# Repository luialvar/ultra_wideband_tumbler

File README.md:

# Tumbler UWB Subsystem Workspace

This repository organizes the hardware, mechanical-design, power-analysis, embedded-driver, and firmware material for the Tumbler UWB node in the AMADEE-27 university robotics project. The software migration from the older SKITH/DWM1000 platform to a newer STM32L4/DWM3000 PCB is a central part of the work, but it is not the whole project: the repository also captures the PCB, mechanical-integration, power-budget, and bring-up context needed to make the Tumbler subsystem usable.

The project is intentionally split by layer. The legacy folders are kept as engineering references, while the new CubeMX firmware and the Tumbler PCB are the active migration target.

## Project Context: AMADEE-27

This work was developed in the context of a university robotics project preparing a contribution for AMADEE-27, an international Mars analog mission managed by the Austrian Space Forum (OeWF).

AMADEE-27 is designed to emulate selected aspects of a human-robotic Mars mission. The mission concept combines analog astronauts, robotic systems, field experiments, and a Mission Support Center in Austria to recreate operational constraints similar to planetary exploration. The official AMADEE-27 call focuses on areas such as engineering and robotics, planetary surface operations, geoscience, life sciences, and human factors.

Within that broader university project, my responsibility was the Tumbler UWB subsystem rather than only a code port. That included understanding the old UWB localization stack, contributing to mechanical design and integration ideas, helping around the new PCB by studying the schematic/layout and matching it to firmware pin names, learning the practical hardware constraints, documenting the PCB and power-budget context, and preparing the new STM32CubeMX/HAL firmware structure for the upgraded PCB.

External context:

- Austrian Space Forum AMADEE-27 overview: https://oewf.org/en/amadee-27/
- AMADEE-27 Announcement of Opportunity: https://oewf.org/en/2025/12/amadee-27-ao/

## Tumbler Subsystem Scope

The important object in this repository is the Tumbler UWB subsystem as an integrated robot component. In practice, that means the work spans several connected areas:

- mechanical design exploration for fitting the electronics into the Tumbler concept,
- support and learning around the new PCB design, including how schematic/layout choices become firmware pin definitions,
- power-budget tracking for tag and anchor operating assumptions,
- low-level STM32L4/DWM3000 bring-up,
- migration of the old UWB ranging ideas onto a new CubeMX/HAL and Qorvo DW3xxx base.

The firmware migration is therefore one part of a larger embedded-system integration effort.

## Migration Summary

| Layer | Legacy platform | New platform |
| --- | --- | --- |
| Hardware | DWM1000-based SKITH board | DWM3000-based Tumbler board |
| Microcontroller | STM32F407 | STM32L431 |
| Framework | RODOS and legacy board wrappers | STM32Cube HAL generated by CubeMX |
| UWB driver | Decawave DWM1000 API | Qorvo DW3xxx driver |
| Application | Legacy tag/anchor ranging code | New CubeMX firmware for the new PCB |

## Repository Map

| Folder | Purpose |
| --- | --- |
| `SKITH_old_PCB/` | Legacy PCB design for the old SKITH UWB node. It represents the old hardware side of the DWM1000/STM32F407 platform. |
| `Tumbler_new_PCB/` | New PCB design for the upgraded UWB node. It contains the KiCad project, schematic sheets, layout, 3D exports, and production outputs for the DWM3000/STM32L431 board. |
| `power_calculations/` | Spreadsheet-based power budgets. The files are grouped around the old and new PCB assumptions, including anchor/tag operating modes. |
| `old_uwb_reference_repo/` | Legacy university toolkit component used as a software reference. It contains the old embedded DWM1000 firmware plus robot-side ROS localization code. |
| `software_new_pcb/` | New STM32CubeMX/HAL firmware for the new PCB. This is the active new-board software area. |
| `tumbler_images/` | Mechanical concept images and visual material for the Tumbler integration work. |
| `useful_links.txt` | Extra project links and references collected during development. |

## What Is Reused

The useful software inheritance is at the protocol level, not at the low-level driver level. The legacy code is valuable because it already contains the tag/anchor ranging flow, message types, timestamp packing, and two-way-ranging state machine. Those concepts can be ported to the new firmware.

The old Decawave DWM1000 driver, the RODOS scheduling code, the old SPI/GPIO wrappers, and the old board calibration constants should not be copied directly into the new STM32L431/DWM3000 firmware.

## Current Engineering Focus

The new firmware is built around STM32Cube HAL and the Qorvo DW3xxx driver. CubeMX describes the real wiring from the new PCB, including SPI, IRQ, reset, wakeup, power-control, and BMS-related pins. The firmware then uses those generated names in the board-port layer so that the UWB driver can talk to the DWM3000 through the actual hardware connections.

The practical bring-up path is:

1. Validate the CubeMX pin map against the Tumbler PCB schematic.
2. Bring up SPI, reset, wakeup, chip-select, and IRQ in the STM32 port layer.
3. Read the DW3xxx device ID through the Qorvo driver.
4. Test raw TX/RX frames.
5. Port the old tag/anchor ranging logic onto the new driver and HAL base.
6. Recalibrate antenna delays and timing for the new board.

## Engineering Highlights

This repository demonstrates a full embedded migration across hardware, firmware, and tooling boundaries:

- connecting mechanical integration constraints with the electronics layout,
- helping translate the new PCB design into a firmware-facing pin map,
- translating real PCB wiring into CubeMX/HAL pin definitions,
- replacing a legacy DWM1000 driver stack with the Qorvo DW3xxx driver,
- separating reusable ranging logic from non-reusable board/framework code,
- keeping only the required DW3xxx driver sources inside the firmware tree instead of storing the full vendor SDK,
- connecting firmware operating modes to spreadsheet-based power estimates.

## Notes for Reviewers

This repository is a migration and integration workspace, so it intentionally contains both original references and new implementation work. The separation is important: hardware design files document the boards, the power spreadsheets document expected operating modes, and the CubeMX firmware is where the new embedded software and DW3xxx driver integration are implemented.

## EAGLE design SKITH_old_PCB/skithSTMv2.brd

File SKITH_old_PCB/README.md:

# SKITH Old PCB

This folder contains the legacy PCB design for the older SKITH UWB node used as the starting point of the migration.

In the overall project, this is the old hardware reference:

| Layer | Value |
| --- | --- |
| UWB module | DWM1000 |
| Microcontroller family | STM32F407 |
| Firmware stack used with this board | RODOS, legacy wrappers, Decawave DWM1000 API |
| Role in this repository | Hardware reference for the legacy platform |

## Contents

| File or folder | Purpose |
| --- | --- |
| `skithSTMv2.kicad_pro` | KiCad project entry point. Open this file in KiCad to inspect the board. |
| `skithSTMv2.kicad_pcb` | PCB layout. |
| `skithSTMv2.sch` | Legacy schematic file. |
| `Schaltplan_Skith_STM_2.pdf` | PDF schematic export for quick review. |
| `skithSTMv2.brd` | Board file from the older design flow. |
| `sym-lib-table` | KiCad symbol-library configuration. |
| `skithSTMv2.kicad_dru` | KiCad design-rule settings. |
| `skithSTMv2.kicad_prl` | KiCad local/session state; useful for KiCad, but not part of the engineering design itself. |

## How This Fits the Migration

This board is not the firmware target for the new implementation. It is included so the old DWM1000/STM32F407 hardware can be compared against the new DWM3000/STM32L431 design.

The old firmware associated with this hardware is kept separately in `../old_uwb_reference_repo/embedded_uwb/`. The PCB files here describe the electrical design: connectors, MCU pins, UWB module wiring, power rails, and board layout.

For the new board, see `../Tumbler_new_PCB/`.

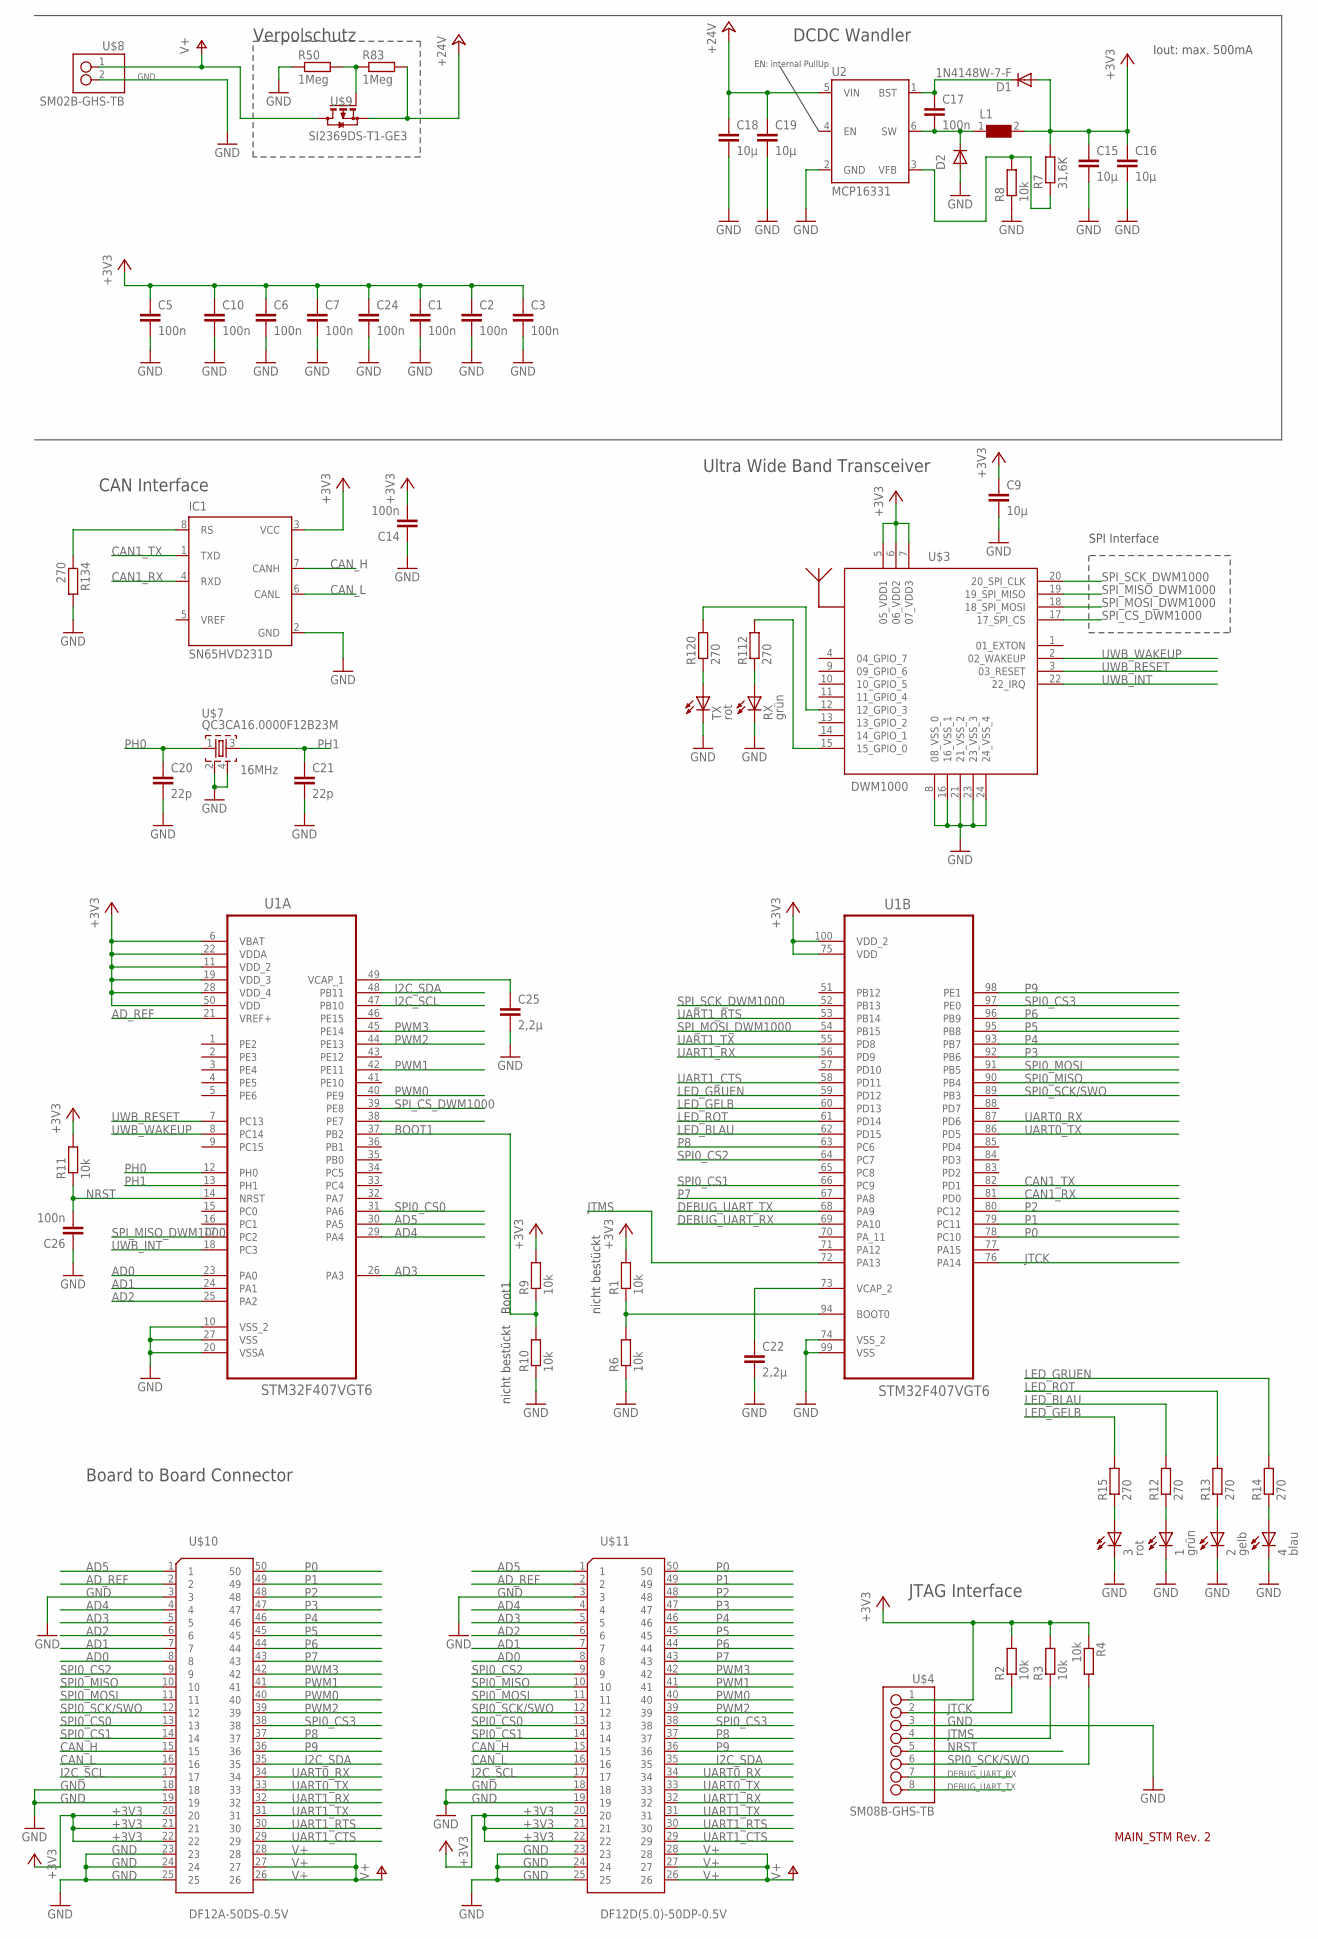
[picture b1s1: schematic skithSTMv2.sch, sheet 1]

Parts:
1: grün; SML0603
2: gelb; SML0603
3: rot; SML0603
4: blau; SML0603
C1, C2, C3, C5, C6, C7, C10, C14, C17, C24, C26: 100n; C0402
C9, C15, C16, C18, C19: 10µ; C0805
C20, C21: 22p; C0402
C22, C25: 2,2µ; C0402
D1: 1N4148W-7-F; SOD123
D2: DIODE-DO214AC; DO214AC
IC1: SN65HVD231D; SO8
L1: WE-TPC-744025150_2828; WE-TPC_2828
R1, R2, R3, R4, R6, R8, R9, R10, R11: 10k; R0402
R7: 31,6K; R0402
R12, R13, R14, R15, R112, R120, R134: 270; R0402
R50, R83: 1Meg; R0402
RX: grün; SML0603
TX: rot; SML0603
U1: STM32F407VGT6; QFP50P1600X1600X160-100N
U2: MCP16331; SOT23-6
U$3: DWM1000
U$4: SM08B-GHS-TB
U$7: QC3CA16.0000F12B23M; LFXTAL055998
U$8: SM02B-GHS-TB
U$9: SI2369DS-T1-GE3; SOT23
U$10: DF12A-50DS-0.5V
U$11: DF12D(5.0)-50DP-0.5V

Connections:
+3V3: C1.1, C2.1, C3.1, C5.1, C6.1, C7.1, C9.1, C10.1, C14.2, C15.1, C16.1, C24.1, D1.A, IC1.3 (VCC), L1.2, R1.2, R2.2, R3.2, R4.1, R7.2, R9.2, R11.2, U1.6 (VBAT), U1.11 (VDD_2), U1.19 (VDD_3), U1.22 (VDDA), U1.28 (VDD_4), U1.50 (VDD), U1.75 (VDD), U1.100 (VDD_2), U$3.5 (05_VDD1), U$3.6 (06_VDD2), U$3.7 (07_VDD3), U$4.1, U$10.20, U$10.21, U$10.22, U$11.20, U$11.21, U$11.22
+24V: C18.1, C19.1, R83.2, U2.5 (VIN), U$9.2 (S)
AD0: U1.23 (PA0), U$10.8, U$11.8
AD1: U1.24 (PA1), U$10.7, U$11.7
AD2: U1.25 (PA2), U$10.6, U$11.6
AD3: U1.26 (PA3), U$10.5, U$11.5
AD4: U1.29 (PA4), U$10.4, U$11.4
AD5: U1.30 (PA5), U$10.1, U$11.1
AD_REF: U1.21 (VREF+), U$10.2, U$11.2
BOOT1: R9.1, R10.2, U1.37 (PB2)
CAN1_RX: IC1.4 (RXD), U1.81 (PD0)
CAN1_TX: IC1.1 (TXD), U1.82 (PD1)
CAN_H: IC1.7 (CANH), U$10.15, U$11.15
CAN_L: IC1.6 (CANL), U$10.16, U$11.16
DEBUG_UART_RX: U1.69 (PA10), U$4.7
DEBUG_UART_TX: U1.68 (PA9), U$4.8
GND: 1.C, 2.C, 3.C, 4.C, C1.2, C2.2, C3.2, C5.2, C6.2, C7.2, C9.2, C10.2, C14.1, C15.2, C16.2, C18.2, C19.2, C20.2, C21.2, C22.2, C24.2, C25.2, C26.1, D2.A, IC1.2 (GND), R6.1, R8.1, R10.1, R50.1, R134.2, RX.C, TX.C, U1.10 (VSS_2), U1.20 (VSSA), U1.27 (VSS), U1.74 (VSS_2), U1.99 (VSS), U2.2 (GND), U$3.8 (08_VSS_0), U$3.16 (16_VSS_1), U$3.21 (21_VSS_2), U$3.23 (23_VSS_3), U$3.24 (24_VSS_4), U$4.3, U$7.2, U$7.4, U$8.2, U$10.3, U$10.18, U$10.19, U$10.23, U$10.24, U$10.25, U$11.3, U$11.18, U$11.19, U$11.23, U$11.24, U$11.25
I2C_SCL: U1.47 (PB10), U$10.17, U$11.17
I2C_SDA: U1.48 (PB11), U$10.35, U$11.35
JTCK: R2.1, U1.76 (PA14), U$4.2
JTMS: R3.1, U1.72 (PA13), U$4.4
LED_BLAU: R12.2, U1.62 (PD15)
LED_GELB: R15.2, U1.60 (PD13)
LED_GRUEN: R14.2, U1.59 (PD12)
LED_ROT: R13.2, U1.61 (PD14)
unnamed: C22.1, U1.73 (VCAP_2)
unnamed: R112.2, U$3.15 (15_GPIO_0)
unnamed: R7.1, R8.2, U2.3 (VFB)
unnamed: C17.1, D1.C, U2.1 (BST)
unnamed: C17.2, D2.C, L1.1, U2.6 (SW)
unnamed: 1.A, R12.1
unnamed: 2.A, R13.1
unnamed: 4.A, R14.1
unnamed: R1.1, R6.2, U1.94 (BOOT0)
unnamed: 3.A, R15.1
unnamed: C25.1, U1.49 (VCAP_1)
unnamed: IC1.8 (RS), R134.1
unnamed: R112.1, RX.A
unnamed: R120.1, TX.A
unnamed: R120.2, U$3.12 (12_GPIO_3)
unnamed: R50.2, R83.1, U$9.1 (G)
NRST: C26.2, R11.1, U1.14 (NRST), U$4.5
P0: U1.78 (PC10), U$10.50, U$11.50
P1: U1.79 (PC11), U$10.49, U$11.49
P2: U1.80 (PC12), U$10.48, U$11.48
P3: U1.92 (PB6), U$10.47, U$11.47
P4: U1.93 (PB7), U$10.46, U$11.46
P5: U1.95 (PB8), U$10.45, U$11.45
P6: U1.96 (PB9), U$10.44, U$11.44
P7: U1.67 (PA8), U$10.43, U$11.43
P8: U1.63 (PC6), U$10.37, U$11.37
P9: U1.98 (PE1), U$10.36, U$11.36
PH0: C20.1, U1.12 (PH0), U$7.1
PH1: C21.1, U1.13 (PH1), U$7.3
PWM0: U1.40 (PE9), U$10.40, U$11.40
PWM1: U1.42 (PE11), U$10.41, U$11.41
PWM2: U1.44 (PE13), U$10.39, U$11.39
PWM3: U1.45 (PE14), U$10.42, U$11.42
SPI0_CS0: U1.31 (PA6), U$10.13, U$11.13
SPI0_CS1: U1.66 (PC9), U$10.14, U$11.14
SPI0_CS2: U1.64 (PC7), U$10.9, U$11.9
SPI0_CS3: U1.97 (PE0), U$10.38, U$11.38
SPI0_MISO: U1.90 (PB4), U$10.10, U$11.10
SPI0_MOSI: U1.91 (PB5), U$10.11, U$11.11
SPI0_SCK/SWO: R4.2, U1.89 (PB3), U$4.6, U$10.12, U$11.12
SPI_CS_DWM1000: U1.39 (PE8), U$3.17 (17_SPI_CS)
SPI_MISO_DWM1000: U1.17 (PC2), U$3.19 (19_SPI_MISO)
SPI_MOSI_DWM1000: U1.54 (PB15), U$3.18 (18_SPI_MOSI)
SPI_SCK_DWM1000: U1.52 (PB13), U$3.20 (20_SPI_CLK)
UART0_RX: U1.87 (PD6), U$10.34, U$11.34
UART0_TX: U1.86 (PD5), U$10.33, U$11.33
UART1_CTS: U1.58 (PD11), U$10.29, U$11.29
UART1_RTS: U1.53 (PB14), U$10.30, U$11.30
UART1_RX: U1.56 (PD9), U$10.32, U$11.32
UART1_TX: U1.55 (PD8), U$10.31, U$11.31
UWB_INT: U1.18 (PC3), U$3.22 (22_IRQ)
UWB_RESET: U1.7 (PC13), U$3.3 (03_RESET)
UWB_WAKEUP: U1.8 (PC14), U$3.2 (02_WAKEUP)
V+: U$8.1, U$9.3 (D), U$10.26, U$10.27, U$10.28, U$11.26, U$11.27, U$11.28

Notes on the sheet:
DCDC Wandler
SPI Interface
Ultra Wide Band Transceiver
CAN Interface
EN: internal PullUp
Verpolschutz
16MHz
JTAG Interface
Board to Board Connector
Iout: max. 500mA
nicht bestückt
Boot1
MAIN_STM Rev. 2

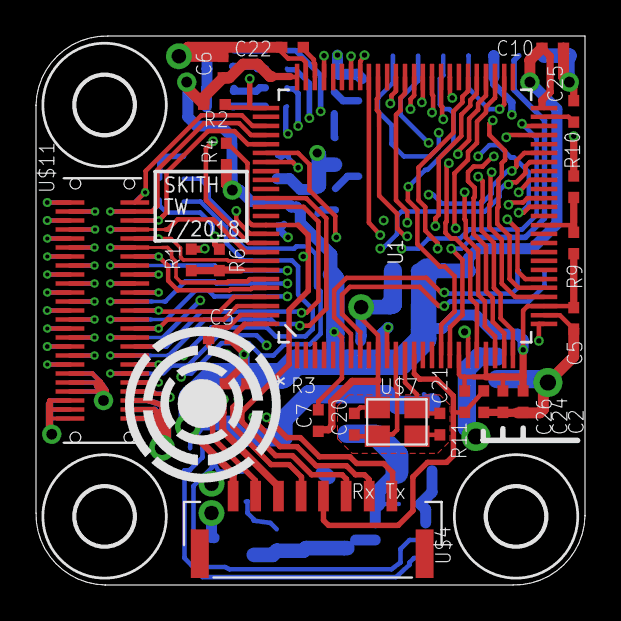
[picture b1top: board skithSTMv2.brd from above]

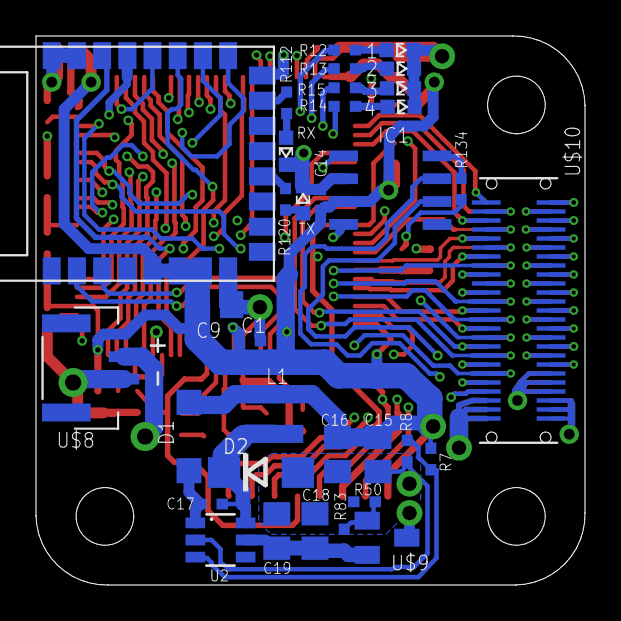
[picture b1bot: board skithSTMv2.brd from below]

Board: 4 copper layers, 30.5 x 30.5 mm, 61 parts (34 on the bottom side), 79 nets.

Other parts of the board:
U$1, U$5, U$6: 3,2

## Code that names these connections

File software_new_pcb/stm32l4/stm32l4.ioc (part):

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Mcu.Name=STM32L431C(B-C)Tx
Mcu.Package=LQFP48
Mcu.UserName=STM32L431CCTx
PA0.GPIOParameters=GPIO_Label
PA0.GPIO_Label=DWM_IRQ
PA0.Signal=GPXTI0
PA1.GPIOParameters=GPIO_Label
PA1.GPIO_Label=BMS_QONn
PA1.Signal=GPIO_Output
PA10.GPIOParameters=GPIO_Label
PA10.GPIO_Label=BMS_SDA
PA10.Mode=I2C
PA10.Signal=I2C1_SDA
PA13\ (JTMS-SWDIO).Mode=Trace_Asynchronous_SW
PA13\ (JTMS-SWDIO).Signal=SYS_JTMS-SWDIO
PA14\ (JTCK-SWCLK).Mode=Trace_Asynchronous_SW
PA14\ (JTCK-SWCLK).Signal=SYS_JTCK-SWCLK
PA2.GPIOParameters=GPIO_Label
PA2.GPIO_Label=BMS_INT
PA2.Signal=GPIO_Input
PA3.Signal=ADCx_IN8
PA4.GPIOParameters=GPIO_Speed,GPIO_PuPd,GPIO_Label
PA4.GPIO_Label=SPI1_NSS
PA4.GPIO_PuPd=GPIO_PULLUP
PA4.GPIO_Speed=GPIO_SPEED_FREQ_MEDIUM
PA4.Signal=GPIO_Output
PA5.Mode=Full_Duplex_Master
PA5.Signal=SPI1_SCK
PA6.Mode=Full_Duplex_Master
PA6.Signal=SPI1_MISO
PA7.Mode=Full_Duplex_Master
PA7.Signal=SPI1_MOSI
PA9.GPIOParameters=GPIO_Label
PA9.GPIO_Label=BMS_SCL
PA9.Mode=I2C
PA9.Signal=I2C1_SCL
PB0.GPIOParameters=GPIO_Label
PB0.GPIO_Label=EXTON
PB0.Signal=GPIO_Output
PB1.GPIOParameters=GPIO_Speed,GPIO_Label
PB1.GPIO_Label=WAKEUP
PB1.GPIO_Speed=GPIO_SPEED_FREQ_MEDIUM
PB1.Signal=GPIO_Output
PB2.GPIOParameters=PinState,GPIO_Label
PB2.GPIO_Label=DWM_nRST
PB2.PinState=GPIO_PIN_SET
PB2.Signal=GPIO_Output
PB3\ (JTDO-TRACESWO).Mode=Trace_Asynchronous_SW
PB3\ (JTDO-TRACESWO).Signal=SYS_JTDO-SWO
PC13.GPIOParameters=GPIO_Label
PC13.GPIO_Label=Buck_EN
PC13.Signal=GPIO_Output
PC14-OSC32_IN\ (PC14).Mode=LSE-External-Oscillator
PC14-OSC32_IN\ (PC14).Signal=RCC_OSC32_IN
PC15-OSC32_OUT\ (PC15).Mode=LSE-External-Oscillator
PC15-OSC32_OUT\ (PC15).Signal=RCC_OSC32_OUT
PH0-OSC_IN\ (PH0).Mode=HSE-External-Oscillator
PH0-OSC_IN\ (PH0).Signal=RCC_OSC_IN
PH1-OSC_OUT\ (PH1).Mode=HSE-External-Oscillator
PH1-OSC_OUT\ (PH1).Signal=RCC_OSC_OUT
RCC.HSE_VALUE=8000000
RCC.SYSCLKFreq_VALUE=80000000
RCC.SYSCLKSource=RCC_SYSCLKSOURCE_PLLCLK
board=custom
